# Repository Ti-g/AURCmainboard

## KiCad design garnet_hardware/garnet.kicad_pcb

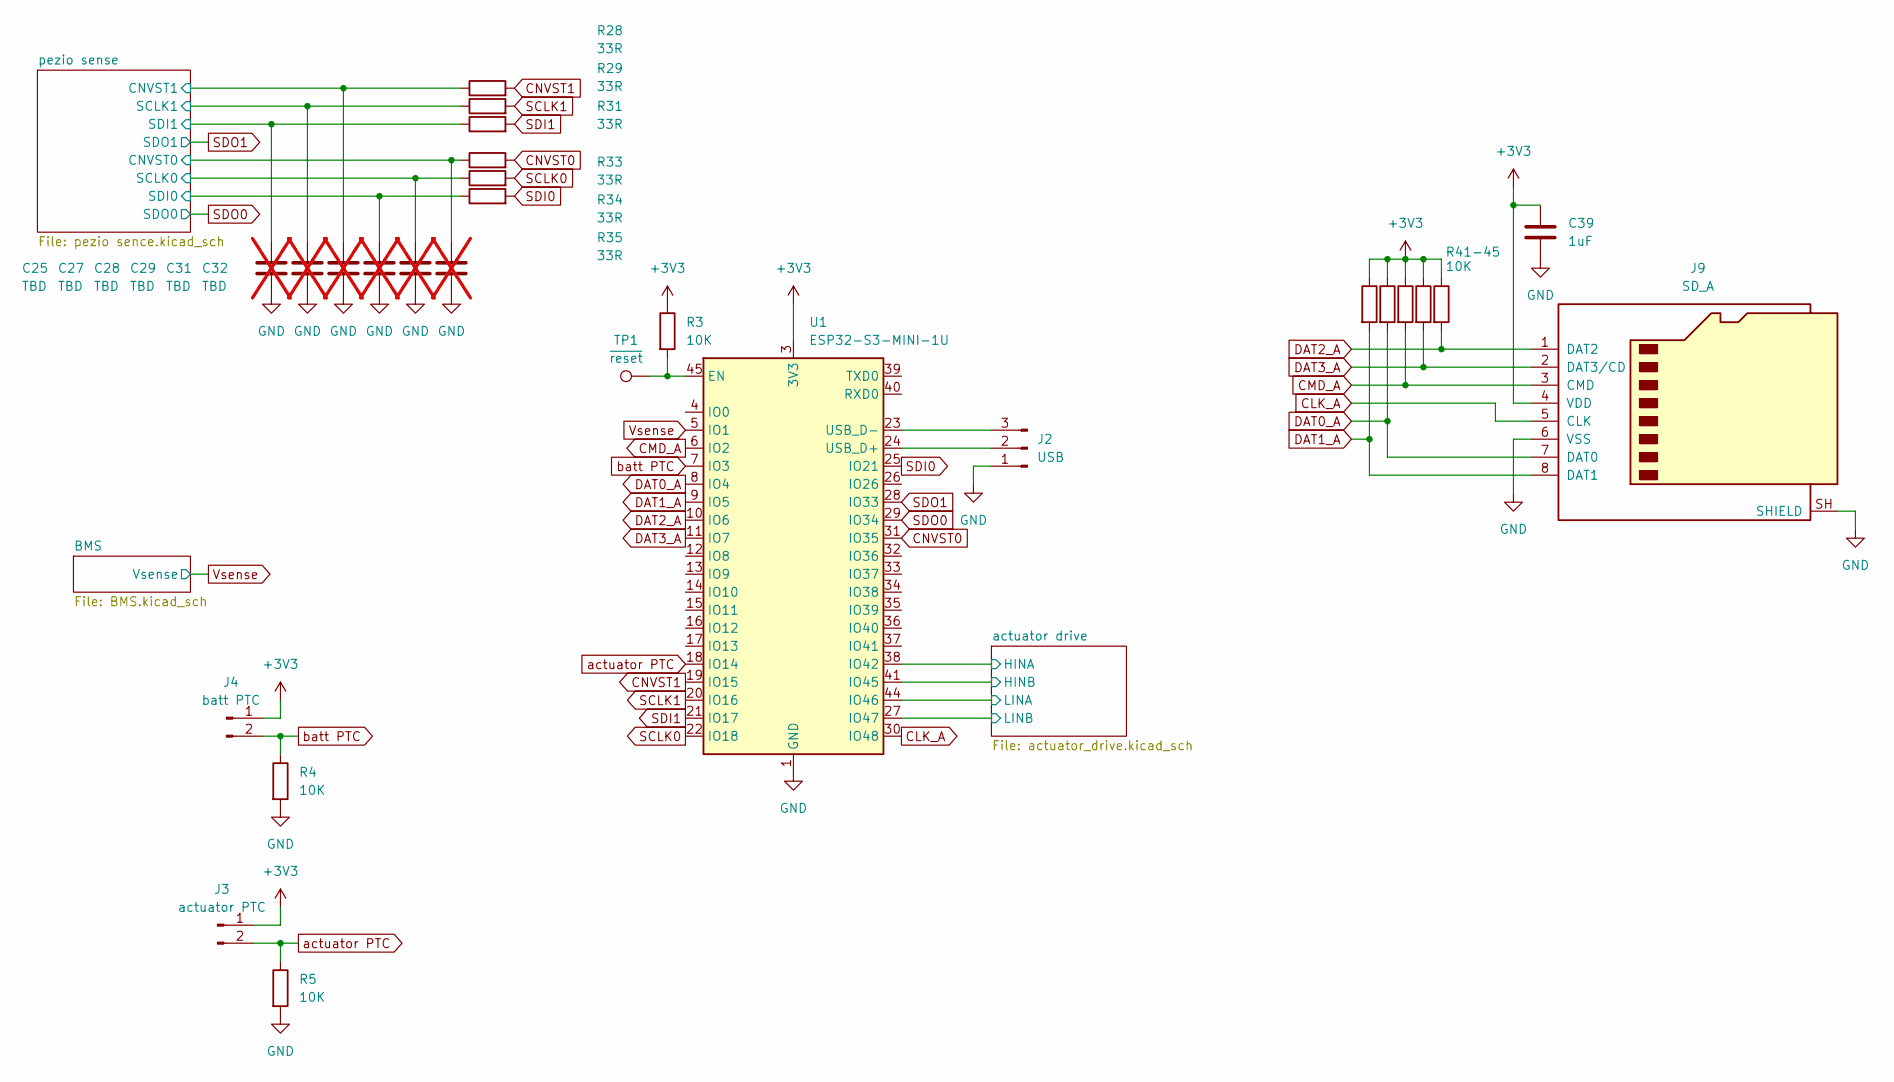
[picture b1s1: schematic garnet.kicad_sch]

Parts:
C25, C27, C28, C29, C31, C32: TBD; C_0603_1608Metric_Pad1.08x0.95mm_HandSolder; not fitted
C39: 1uF; C_0603_1608Metric_Pad1.08x0.95mm_HandSolder
J2: USB; PinHeader_1x03_P2.54mm_Vertical
J3: actuator PTC; PinHeader_1x02_P2.54mm_Horizontal
J4: batt PTC; PinHeader_1x02_P2.54mm_Horizontal
J9: SD_A; microSD_HC_Molex_47219-2001
R3, R4, R5, R41, R41-45, R42, R43, R44: 10K; R_0603_1608Metric_Pad0.98x0.95mm_HandSolder
R28, R29, R31, R33, R34, R35: 33R; R_0603_1608Metric_Pad0.98x0.95mm_HandSolder
TP1: ~{reset}; PinHeader_1x01_P2.54mm_Vertical
U1: ESP32-S3-MINI-1U; ESP32-S2-MINI-1U

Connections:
+3V3: C39.1, J3.1, J4.1, J9.4 (VDD), R3.1, R41.1, R41-45.1, R42.1, R43.1, R44.1, U1.3 (3V3); also elsewhere on the board
/actuator drive/HINA: U1.38 (IO42); also elsewhere on the board
/actuator drive/HINB: U1.41 (IO45); also elsewhere on the board
/actuator drive/LINA: U1.44 (IO46); also elsewhere on the board
/actuator drive/LINB: U1.27 (IO47); also elsewhere on the board
/pezio sense/CNVST0: C32.1, R33.1; also elsewhere on the board
/pezio sense/CNVST1: C28.1, R28.1; also elsewhere on the board
/pezio sense/SCLK0: C31.1, R34.1; also elsewhere on the board
/pezio sense/SCLK1: C27.1, R29.1; also elsewhere on the board
/pezio sense/SDI0: C29.1, R35.1; also elsewhere on the board
/pezio sense/SDI1: C25.1, R31.1; also elsewhere on the board
CLK_A: J9.5 (CLK), U1.30 (IO48)
CMD_A: J9.3 (CMD), R43.2, U1.6 (IO2)
CNVST0: R33.2, U1.31 (IO35)
CNVST1: R28.2, U1.19 (IO15)
DAT0_A: J9.7 (DAT0), R42.2, U1.8 (IO4)
DAT1_A: J9.8 (DAT1), R41.2, U1.9 (IO5)
DAT2_A: J9.1 (DAT2), R41-45.2, U1.10 (IO6)
DAT3_A: J9.2 (DAT3/CD), R44.2, U1.11 (IO7)
GND: C25.2, C27.2, C28.2, C29.2, C31.2, C32.2, C39.2, J2.1, J9.6 (VSS), J9.SH (SHIELD), R4.2, R5.2, U1.1 (GND), U1.2 (GND), U1.42 (GND), U1.43 (GND), U1.46 (GND), U1.47 (GND), U1.48 (GND), U1.49 (GND), U1.50 (GND), U1.51 (GND), U1.52 (GND), U1.53 (GND), U1.54 (GND), U1.55 (GND), U1.56 (GND), U1.57 (GND), U1.58 (GND), U1.59 (GND), U1.60 (GND), U1.61 (GND), U1.62 (GND), U1.63 (GND), U1.64 (GND), U1.65 (GND); also elsewhere on the board
unnamed: J2.2, U1.24 (USB_D+)
unnamed: J2.3, U1.23 (USB_D-)
unnamed: R3.2, TP1.1 (1_1), U1.45 (EN)
SCLK0: R34.2, U1.22 (IO18)
SCLK1: R29.2, U1.20 (IO16)
SDI0: R35.2, U1.25 (IO21)
SDI1: R31.2, U1.21 (IO17)
SDO0: U1.29 (IO34); also elsewhere on the board
SDO1: U1.28 (IO33); also elsewhere on the board
Vsense: U1.5 (IO1); also elsewhere on the board
actuator PTC: J3.2, R5.1, U1.18 (IO14)
batt PTC: J4.2, R4.1, U1.7 (IO3)

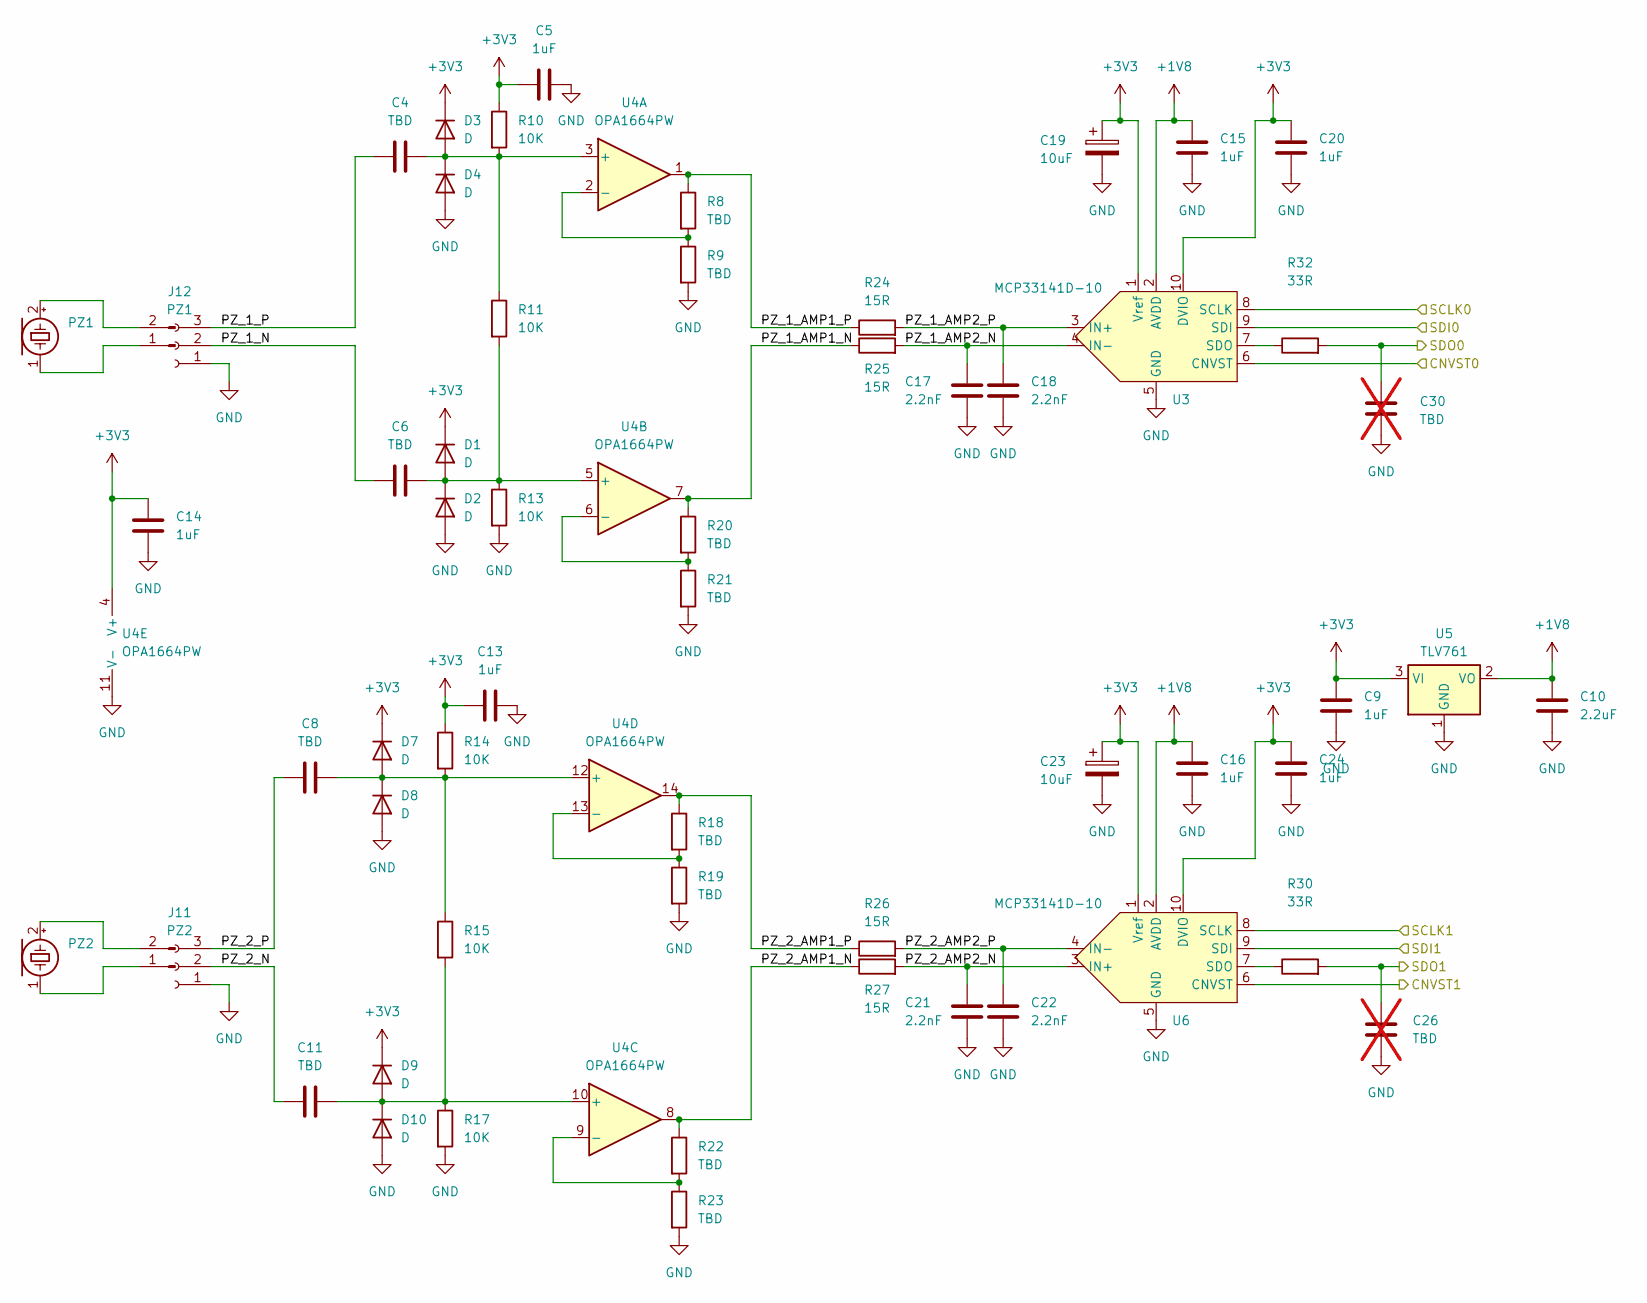
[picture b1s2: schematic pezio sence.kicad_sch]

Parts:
C4, C6, C8, C11: TBD; C_0603_1608Metric_Pad1.08x0.95mm_HandSolder
C5, C9, C20, C24: 1uF; C_0603_1608Metric_Pad1.08x0.95mm_HandSolder
C10: 2.2uF; C_0603_1608Metric_Pad1.08x0.95mm_HandSolder
C13, C14, C15, C16: 1uF; C_0603_1608Metric
C17, C18: 2.2nF; C_0603_1608Metric
C19, C23: 10uF; CP_EIA-3216-10_Kemet-I_HandSolder
C21, C22: 2.2nF; C_0603_1608Metric_Pad1.08x0.95mm_HandSolder
C26, C30: TBD; C_0603_1608Metric_Pad1.08x0.95mm_HandSolder; not fitted
D1, D2, D3, D4, D7, D8, D9, D10: D; D_0603_1608Metric_Pad1.05x0.95mm_HandSolder
J6, J7: Conn_01x02_Pin
J11: PZ2; PinHeader_1x03_P2.54mm_Horizontal
J12: PZ1; PinHeader_1x03_P2.54mm_Horizontal
PZ1, PZ2: (no value)
R8, R9, R18, R19, R20, R21, R22, R23: TBD; R_0603_1608Metric_Pad0.98x0.95mm_HandSolder
R10, R11, R13, R14, R15, R17: 10K; R_0603_1608Metric_Pad0.98x0.95mm_HandSolder
R24, R25, R26, R27: 15R; R_0603_1608Metric_Pad0.98x0.95mm_HandSolder
R30, R32: 33R; R_0603_1608Metric_Pad0.98x0.95mm_HandSolder
U3, U6: MCP33141D-10; MSOP-10_3x3mm_P0.5mm
U4: OPA1664PW; TSSOP-14_4.4x5mm_P0.65mm
U5: TLV761; SOT-223-3_TabPin2

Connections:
+1V8: C10.1, C15.1, C16.1, U3.2 (AVDD), U5.2 (VO), U6.2 (AVDD)
+3V3: C5.1, C9.1, C13.1, C14.1, C19.1, C20.1, C23.1, C24.1, D1.1 (K), D3.1 (K), D7.1 (K), D9.1 (K), R10.1, R14.1, U3.1 (Vref), U3.10 (DVIO), U4.4 (V+), U5.3 (VI), U6.1 (Vref), U6.10 (DVIO); also elsewhere on the board
/pezio sense/CNVST0: U3.6 (CNVST); also elsewhere on the board
/pezio sense/CNVST1: U6.6 (CNVST); also elsewhere on the board
/pezio sense/PZ_1_AMP1_N: R20.1, R25.1, U4.7
/pezio sense/PZ_1_AMP1_P: R8.1, R24.1, U4.1
/pezio sense/PZ_1_AMP2_N: C17.1, R25.2, U3.4 (IN-)
/pezio sense/PZ_1_AMP2_P: C18.1, R24.2, U3.3 (IN+)
/pezio sense/PZ_1_N: C6.1, J12.2
/pezio sense/PZ_1_P: C4.1, J12.3
/pezio sense/PZ_2_AMP1_N: R22.1, R27.1, U4.8
/pezio sense/PZ_2_AMP1_P: R18.1, R26.1, U4.14
/pezio sense/PZ_2_AMP2_N: C21.1, R27.2, U6.3 (IN+)
/pezio sense/PZ_2_AMP2_P: C22.1, R26.2, U6.4 (IN-)
/pezio sense/PZ_2_N: C11.1, J11.2
/pezio sense/PZ_2_P: C8.1, J11.3
/pezio sense/SCLK0: U3.8 (SCLK); also elsewhere on the board
/pezio sense/SCLK1: U6.8 (SCLK); also elsewhere on the board
/pezio sense/SDI0: U3.9 (SDI); also elsewhere on the board
/pezio sense/SDI1: U6.9 (SDI); also elsewhere on the board
GND: C5.2, C9.2, C10.2, C13.2, C14.2, C15.2, C16.2, C17.2, C18.2, C19.2, C20.2, C21.2, C22.2, C23.2, C24.2, C26.2, C30.2, D2.2 (A), D4.2 (A), D8.2 (A), D10.2 (A), J11.1, J12.1, R9.2, R13.2, R17.2, R19.2, R21.2, R23.2, U3.5 (GND), U4.11 (V-), U5.1 (GND), U6.5 (GND); also elsewhere on the board
unnamed: C6.2, D1.2 (A), D2.1 (K), R11.2, R13.1, U4.5 (+)
unnamed: C4.2, D3.2 (A), D4.1 (K), R10.2, R11.1, U4.3 (+)
unnamed: C8.2, D7.2 (A), D8.1 (K), R14.2, R15.1, U4.12 (+)
unnamed: C11.2, D9.2 (A), D10.1 (K), R15.2, R17.1, U4.10 (+)
unnamed: J6.1, PZ1.1 (-)
unnamed: J6.2, PZ1.2 (+)
unnamed: J7.1, PZ2.1 (-)
unnamed: J7.2, PZ2.2 (+)
unnamed: R32.1, U3.7 (SDO)
unnamed: R8.2, R9.1, U4.2 (-)
unnamed: R20.2, R21.1, U4.6 (-)
unnamed: R22.2, R23.1, U4.9 (-)
unnamed: R18.2, R19.1, U4.13 (-)
unnamed: R30.1, U6.7 (SDO)
SDO0: C30.1, R32.2; also elsewhere on the board
SDO1: C26.1, R30.2; also elsewhere on the board

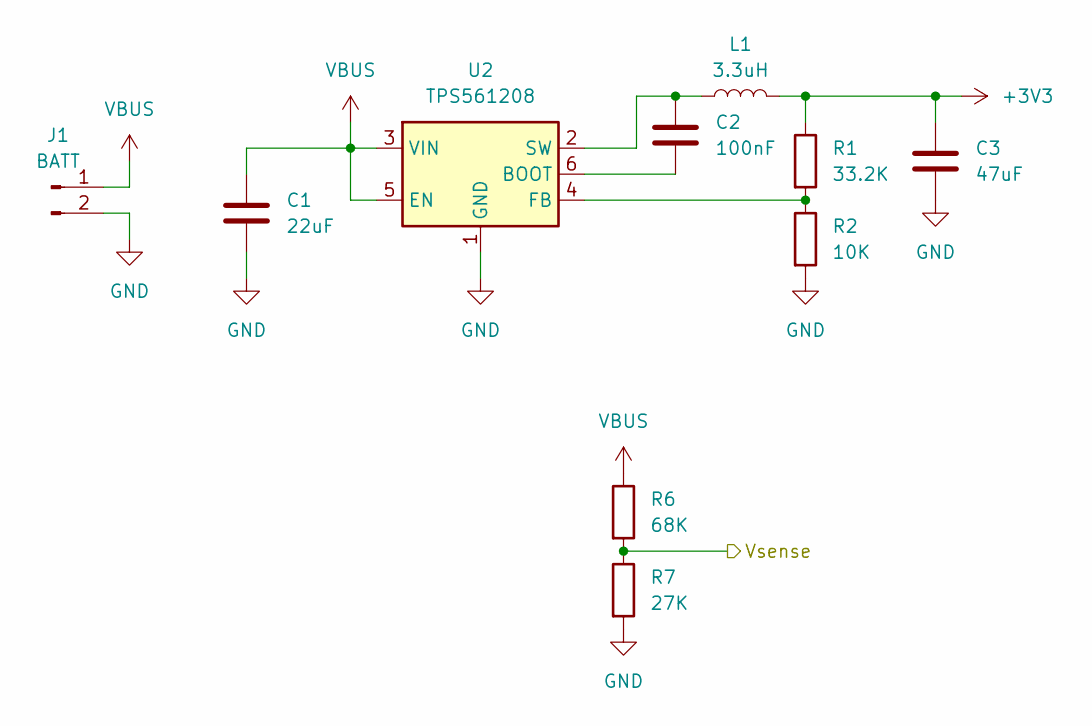
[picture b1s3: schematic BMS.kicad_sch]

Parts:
C1: 22uF; C_0603_1608Metric_Pad1.08x0.95mm_HandSolder
C2: 100nF; C_0603_1608Metric_Pad1.08x0.95mm_HandSolder
C3: 47uF; C_0603_1608Metric_Pad1.08x0.95mm_HandSolder
J1: BATT; AMASS_XT60PW-F_1x02_P7.20mm_Horizontal
L1: 3.3uH; L_Neosid_SMS-ME3010
R1: 33.2K; R_0603_1608Metric_Pad0.98x0.95mm_HandSolder
R2: 10K; R_0603_1608Metric_Pad0.98x0.95mm_HandSolder
R6: 68K; R_0603_1608Metric_Pad0.98x0.95mm_HandSolder
R7: 27K; R_0603_1608Metric_Pad0.98x0.95mm_HandSolder
U2: TPS561208; SOT-23-6

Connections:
+3V3: C3.1, L1.2, R1.1; also elsewhere on the board
GND: C1.2, C3.2, J1.2, R2.2, R7.2, U2.1 (GND); also elsewhere on the board
unnamed: C2.1, U2.6 (BOOT)
unnamed: R1.2, R2.1, U2.4 (FB)
unnamed: C2.2, L1.1, U2.2 (SW)
VBUS: C1.1, J1.1, R6.1, U2.3 (VIN), U2.5 (EN); also elsewhere on the board
Vsense: R6.2, R7.1; also elsewhere on the board

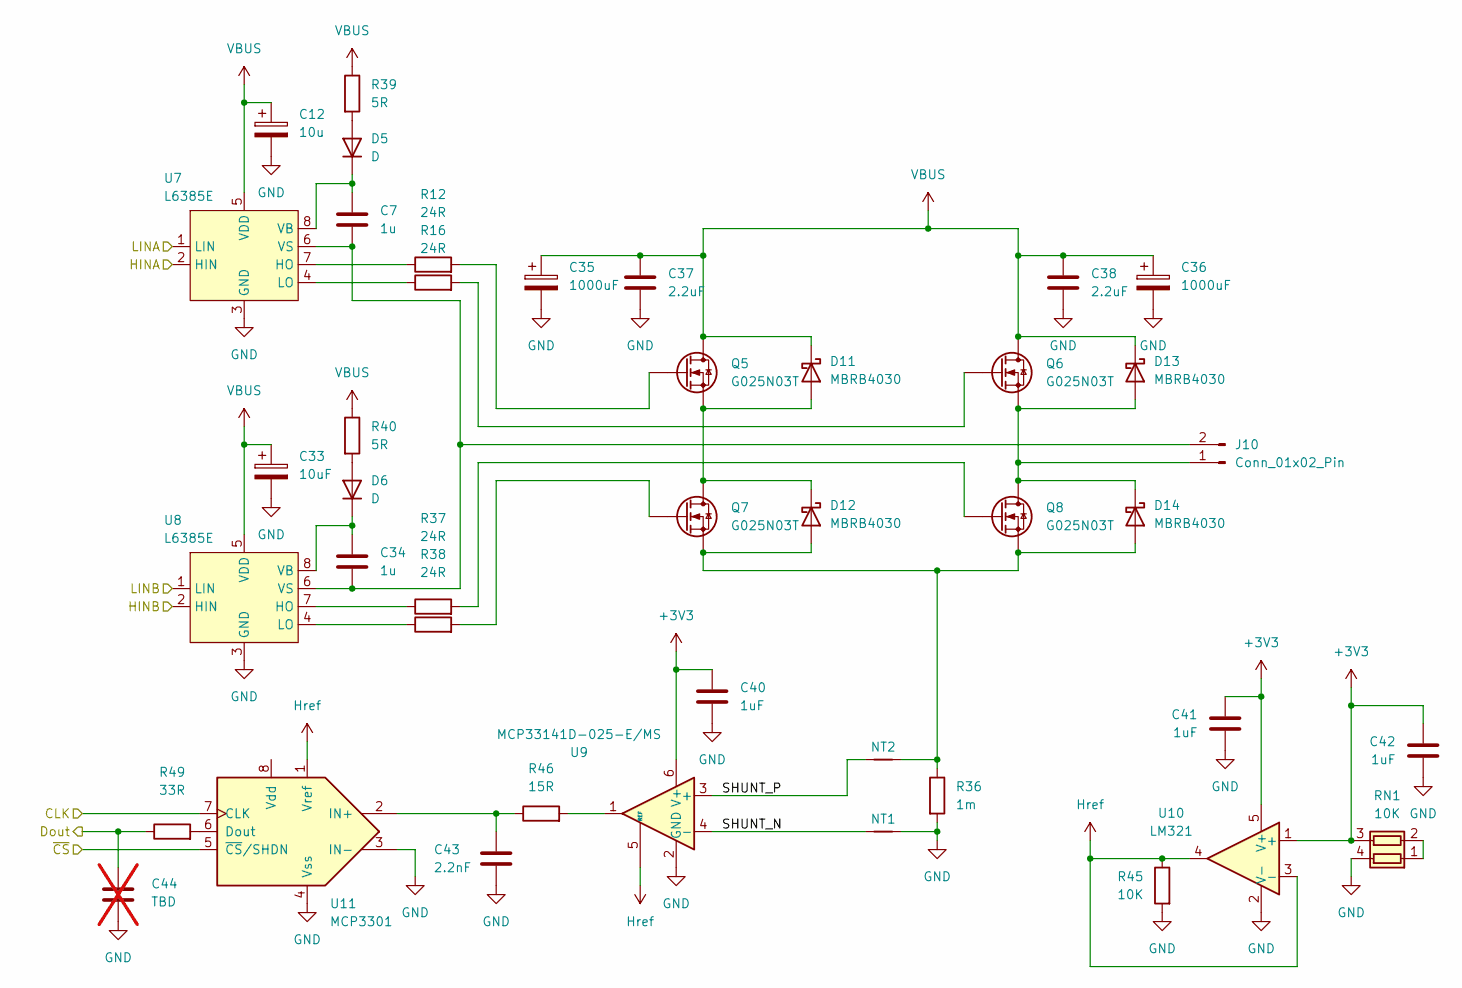
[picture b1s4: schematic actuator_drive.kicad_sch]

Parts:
C7, C34: 1u; C_0603_1608Metric_Pad1.08x0.95mm_HandSolder
C12: 10u; CP_Elec_4x4.5
C33: 10uF; CP_Elec_4x4.5
C35, C36: 1000uF; CP_Elec_10x12.5
C37, C38: 2.2uF; C_0603_1608Metric_Pad1.08x0.95mm_HandSolder
C40, C41, C42: 1uF; C_0603_1608Metric_Pad1.08x0.95mm_HandSolder
C43: 2.2nF; C_0603_1608Metric_Pad1.08x0.95mm_HandSolder
C44: TBD; C_0603_1608Metric_Pad1.08x0.95mm_HandSolder; not fitted
D5, D6: D; D_0603_1608Metric_Pad1.05x0.95mm_HandSolder
D11, D12, D13, D14: MBRB4030; TO-263-2
J10: Conn_01x02_Pin; AMASS_XT60PW-F_1x02_P7.20mm_Horizontal
NT1, NT2: (no value)
Q5, Q6, Q7, Q8: G025N03T; TO-220-3_Vertical
R12, R16, R37, R38: 24R; R_0603_1608Metric_Pad0.98x0.95mm_HandSolder
R36: 1m; R_2512_6332Metric_Pad1.40x3.35mm_HandSolder
R39, R40: 5R; R_0603_1608Metric_Pad0.98x0.95mm_HandSolder
R45: 10K
R46: 15R; R_0603_1608Metric_Pad0.98x0.95mm_HandSolder
R49: 33R; R_0603_1608Metric_Pad0.98x0.95mm_HandSolder
RN1: 10K; R_Array_Convex_2x0606
U7, U8: L6385E; SOIC-8_5.3x5.3mm_P1.27mm
U9: MCP33141D-025-E/MS; MSOP-10_3x3mm_P0.5mm
U10: LM321; SOT-23-5
U11: MCP3301

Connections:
+3V3: C40.2, C41.2, C42.2, RN1.3 (R2.2), U9.6 (V+), U10.1 (+), U10.5 (V+); also elsewhere on the board
/actuator drive/Dout: C44.1, R49.1
/actuator drive/HINA: U7.2 (HIN); also elsewhere on the board
/actuator drive/HINB: U8.2 (HIN); also elsewhere on the board
/actuator drive/LINA: U7.1 (LIN); also elsewhere on the board
/actuator drive/LINB: U8.1 (LIN); also elsewhere on the board
/actuator drive/SHUNT_N: NT1.1, U9.4 (-)
/actuator drive/SHUNT_P: NT2.1, U9.3 (+)
GND: C12.2, C33.2, C35.2, C36.2, C37.2, C38.2, C40.1, C41.1, C42.1, C43.2, C44.2, NT1.2, R36.2, R45.2, RN1.4 (R1.2), U7.3 (GND), U8.3 (GND), U9.2 (GND), U10.2 (V-), U11.3 (IN-), U11.4 (Vss); also elsewhere on the board
Href: R45.1, U9.5 (REF), U10.3 (-), U10.4, U11.1 (Vref)
unnamed: D5.2 (A), R39.2
unnamed: C7.1, D5.1 (K), U7.8 (VB)
unnamed: D6.2 (A), R40.2
unnamed: C34.1, D6.1 (K), U8.8 (VB)
unnamed: D11.2 (A), D12.1 (K), Q5.3 (S), Q7.2 (D)
unnamed: D12.2 (A), D14.2 (A), NT2.2, Q7.3 (S), Q8.3 (S), R36.1
unnamed: D13.2 (A), D14.1 (K), J10.1, Q6.3 (S), Q8.2 (D)
unnamed: C7.2, C34.2, J10.2, U7.6 (VS), U8.6 (VS)
unnamed: Q5.1 (G), R12.2
unnamed: Q6.1 (G), R16.2
unnamed: Q7.1 (G), R38.2
unnamed: Q8.1 (G), R37.2
unnamed: R46.2, U9.1
unnamed: RN1.1 (R1.1), RN1.2 (R2.1)
unnamed: R12.1, U7.7 (HO)
unnamed: R16.1, U7.4 (LO)
unnamed: R37.1, U8.7 (HO)
unnamed: R38.1, U8.4 (LO)
unnamed: R49.2, U11.6 (Dout)
unnamed: C43.1, R46.1, U11.2 (IN+)
VBUS: C12.1, C33.1, C35.1, C36.1, C37.1, C38.1, D11.1 (K), D13.1 (K), Q5.2 (D), Q6.2 (D), R39.1, R40.1, U7.5 (VDD), U8.5 (VDD); also elsewhere on the board

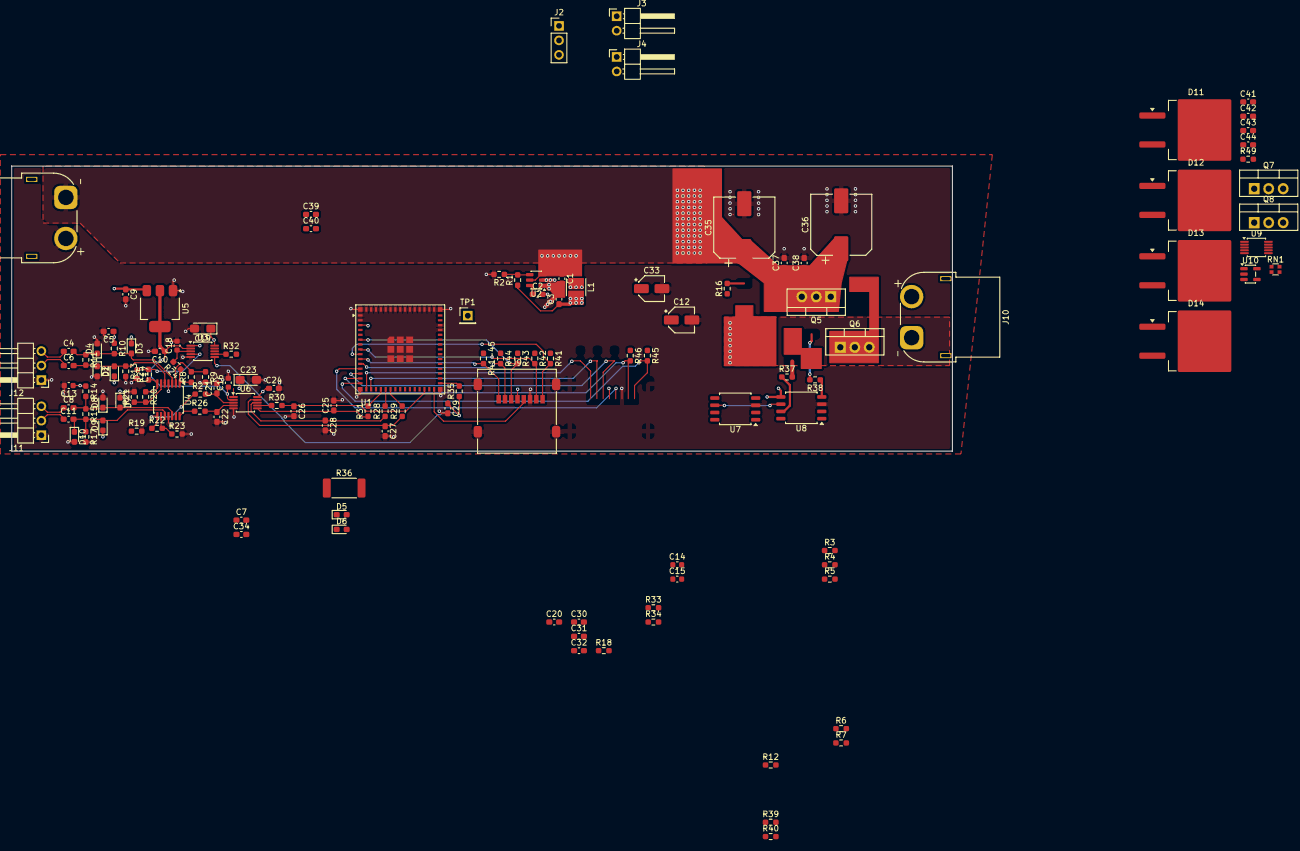
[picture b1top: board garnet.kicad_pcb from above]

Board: 4 copper layers, 165.0 x 50.0 mm, 131 parts (0 on the bottom side), 80 nets.
